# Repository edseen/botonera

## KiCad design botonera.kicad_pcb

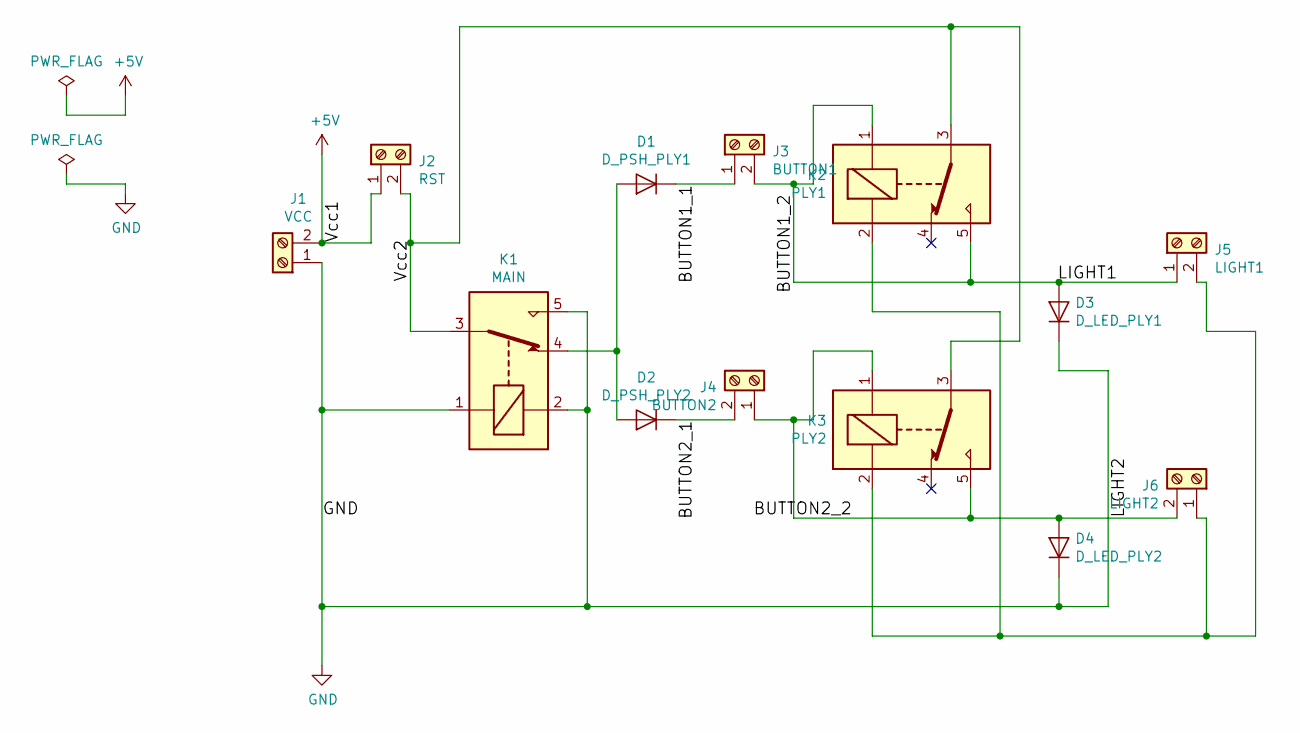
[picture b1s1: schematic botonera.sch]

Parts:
D1: D_PSH_PLY1; D_DO-41_SOD81_P10.16mm_Horizontal
D2: D_PSH_PLY2; D_DO-41_SOD81_P10.16mm_Horizontal
D3: D_LED_PLY1; D_DO-41_SOD81_P10.16mm_Horizontal
D4: D_LED_PLY2; D_DO-41_SOD81_P10.16mm_Horizontal
J1: VCC; TerminalBlock_TE_282834-2_1x02_P2.54mm_Horizontal
J2: RST; TerminalBlock_TE_282834-2_1x02_P2.54mm_Horizontal
J3: BUTTON1; TerminalBlock_TE_282834-2_1x02_P2.54mm_Horizontal
J4: BUTTON2; TerminalBlock_TE_282834-2_1x02_P2.54mm_Horizontal
J5: LIGHT1; TerminalBlock_TE_282834-2_1x02_P2.54mm_Horizontal
J6: LIGHT2; TerminalBlock_TE_282834-2_1x02_P2.54mm_Horizontal
K1: MAIN; Relay_SUNHOLD_RAS_Series_Form_C
K2: PLY1; Relay_SUNHOLD_RAS_Series_Form_C
K3: PLY2; Relay_SUNHOLD_RAS_Series_Form_C

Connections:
+5V: J1.2, J2.1
/BUTTON1_1: D1.1 (K), J3.1
/BUTTON1_2: D3.2 (A), J3.2, J5.1, K2.1 (Coil), K2.5 (NO)
/BUTTON2_1: D2.1 (K), J4.2
/BUTTON2_2: D4.2 (A), J4.1, J6.2, K3.1 (Coil), K3.5 (NO)
/Vcc2: J2.2, K1.3 (Common), K2.3 (Common), K3.3 (Common)
GND: D3.1 (K), D4.1 (K), J1.1, K1.1 (Coil), K1.2 (Coil), K1.5 (NO)
unnamed: D1.2 (A), D2.2 (A), K1.4 (NC)
unnamed: J5.2, J6.1, K2.2 (Coil), K3.2 (Coil)

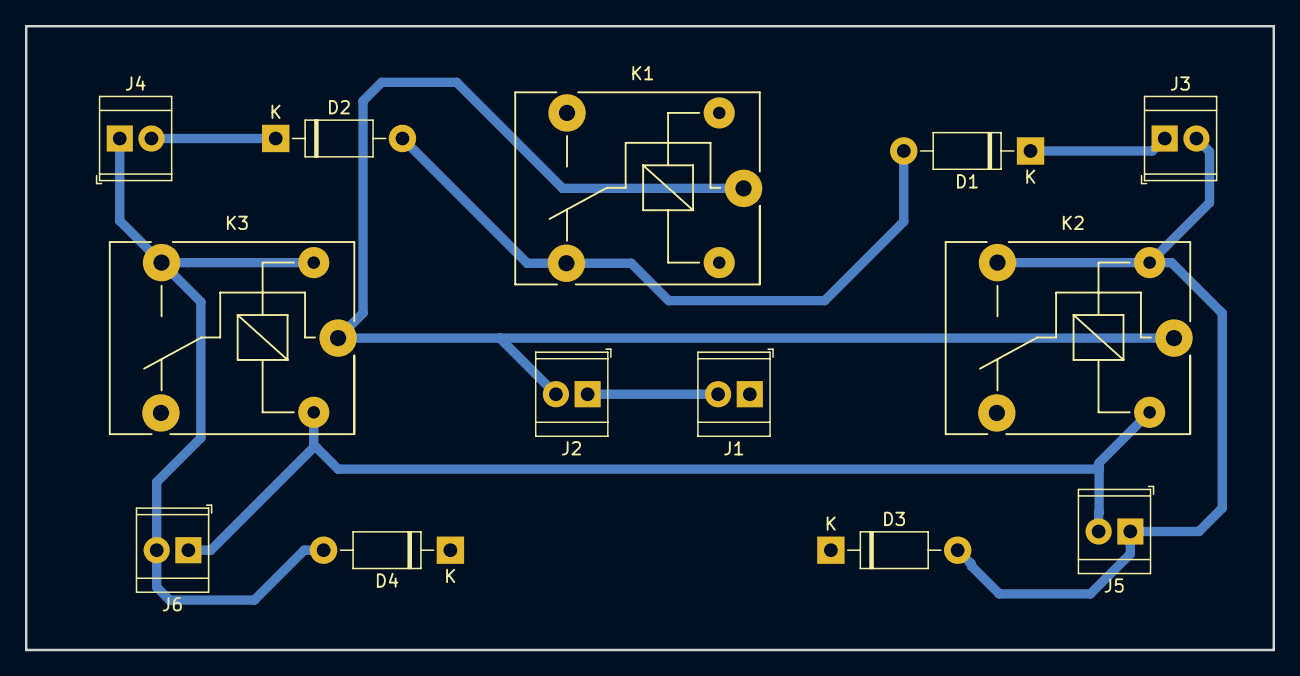
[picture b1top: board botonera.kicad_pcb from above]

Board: 2 copper layers, 100.0 x 50.0 mm, 13 parts (0 on the bottom side), 9 nets.

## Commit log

2017-12-07 Esquematico
2017-12-07 Librerias
2017-12-07 Limpieza de librerias
2018-12-06 esquematico y pcb generado
